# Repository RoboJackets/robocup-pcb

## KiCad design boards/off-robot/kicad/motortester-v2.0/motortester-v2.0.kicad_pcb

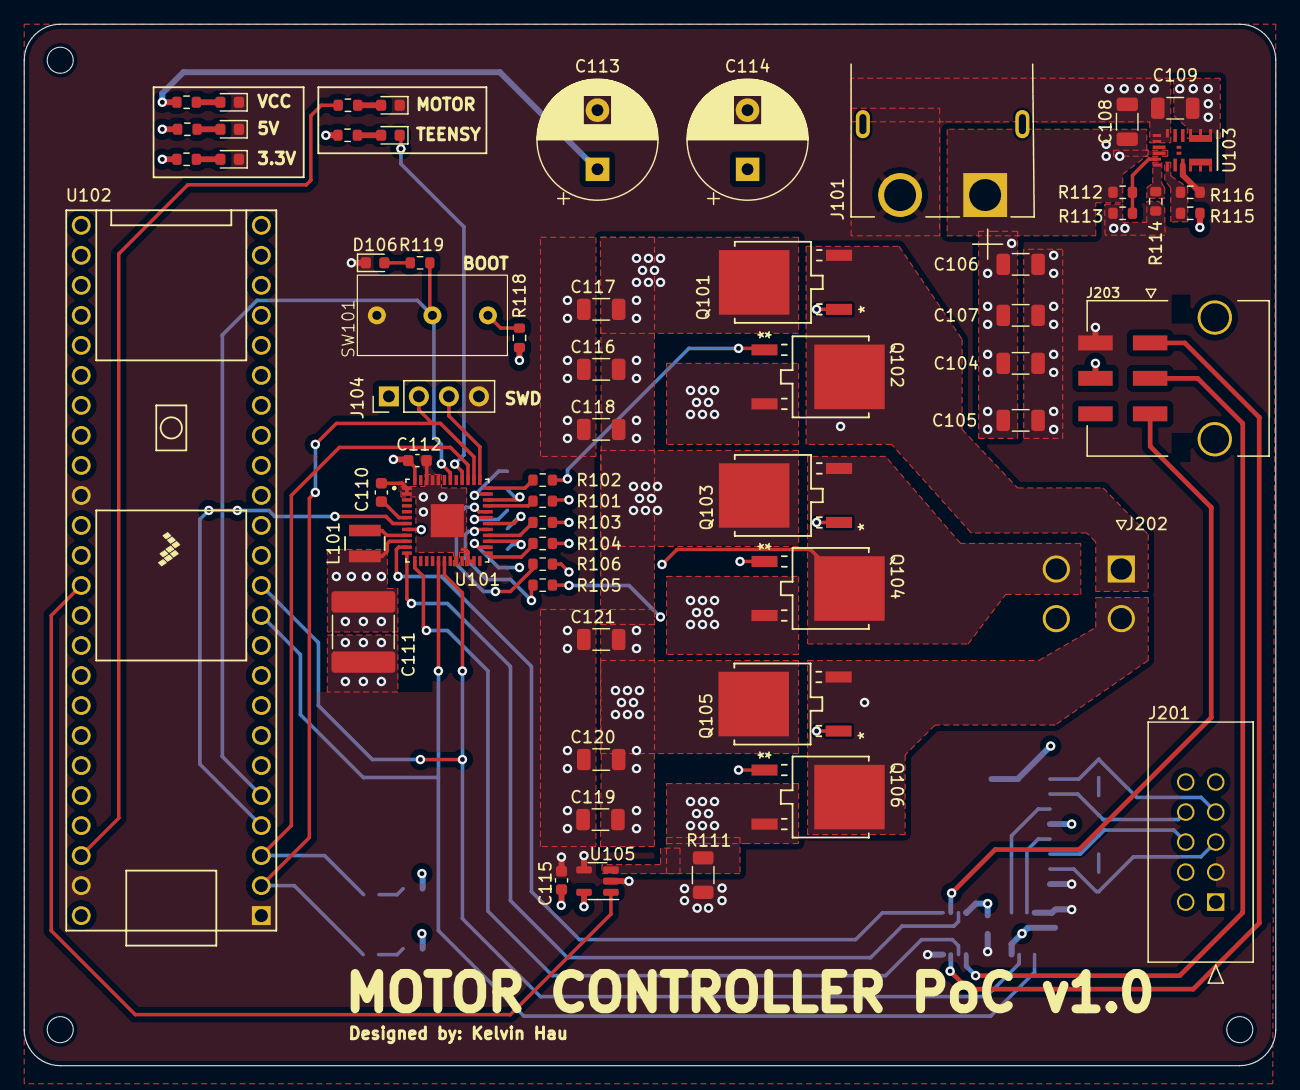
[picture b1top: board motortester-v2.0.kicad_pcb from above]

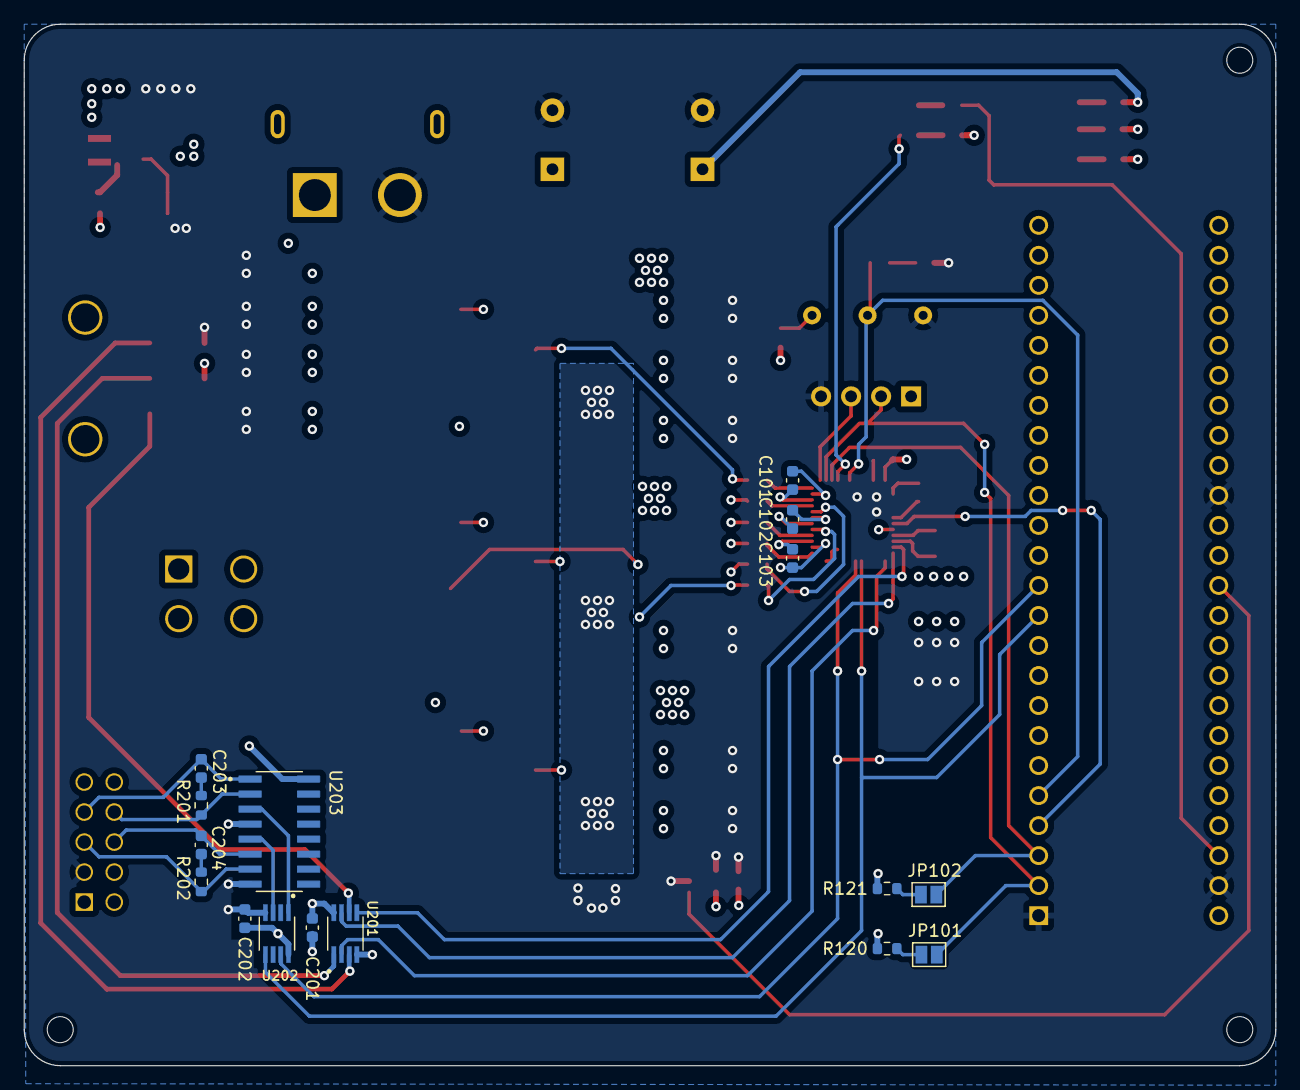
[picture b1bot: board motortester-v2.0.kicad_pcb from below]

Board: 4 copper layers, 105.9 x 88.1 mm, 79 parts (16 on the bottom side), 61 nets.

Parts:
C101, C102, C103, C112, C115, C201, C202: 100nF; C_0603_1608Metric
C104, C105, C106, C107, C108, C116, C117, C118, C119, C120, C121: 10uF; C_1206_3216Metric
C109: 22uF; C_1206_3216Metric
C110: 1uF; C_0603_1608Metric
C111: 47uF; C_2220_5750Metric
C113, C114: 220uF; CP_Radial_D10.0mm_P5.00mm
C203, C204: 0.1nF; C_0603_1608Metric
D101, D102, D103, D104, D105, D106: GREEN; D_0603_1608Metric
H201, H202, H203: MountingHole; MountingHole_2.2mm_M2
J101: XT60PW-M; AMASS_XT60PW-M
J104: SWD; PinHeader_1x04_P2.54mm_Vertical
J201: 702461004; CON_702461004_MOL
J202: 1x4_Molex_Connector; MOLEX_353180420
J203: 430450607; MOLEX_430450607
JP101, JP102: SolderJumper_2_Open; SolderJumper-2_P1.3mm_Open_Pad1.0x1.5mm
L101: 22uH; SRN3015
Q101, Q102, Q103, Q104, Q105, Q106: STD140N6F7; DPAKTO-252_A2_STM
R101, R102, R103, R104, R105, R106, R201, R202: 62; R_0603_1608Metric
R107, R109, R110, R117, R119: 1k; R_0603_1608Metric
R108: 4.7k; R_0603_1608Metric
R111: 2m; R_1206_3216Metric
R112: 270k; R_0603_1608Metric
R113, R120, R121: 100k; R_0603_1608Metric
R114: 63.4k; R_0603_1608Metric
R115: 160k; R_0603_1608Metric
R116: 30.1k; R_0603_1608Metric
R118: 10k; R_0603_1608Metric
SW101: SW_SPDT; Slide_Switch_SPDT
U101: STSPIN32F0A; IC_STSPIN32F0A
U102: Teensy4.1; Teensy41
U103: MPM3620GQV-P
U105: INA180A3; SOT-23-5
U201, U202: SN74LVC3G17DCTR; SOP65P400X130-8N
U203: MC3486DR; SOIC127P600X175-16N

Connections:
+3.3V: C111.1, C112.2, C115.1, C201.1, C202.1, J104.1, L101.1, R109.2, R110.2, R118.1, R120.2, R121.2, U101.10 (VDDA), U101.48 (VDD), U105.5 (V+), U201.8 (VCC), U202.8 (VCC)
+5V: C109.1, J201.2, J203.5, R115.2, R117.2, U102.48 (VIN), U103.7 (OUT), U103.8 (OUT), U103.9 (OUT), U203.4 (1,2EN), U203.16 (VCC)
BOOT_0: R119.2, SW101.2 (B), U101.42 (BOOT0), U102.5 (3_LRCLK2)
ENCA: U101.17 (PA6), U102.11 (9_OUT1C), U202.5 (2Y)
ENCA_N: J201.5, R202.1, U203.7 (2B)
ENCA_O: U202.3 (2A), U203.5 (2Y)
ENCA_P: C204.1, J201.6, U203.6 (2A)
ENCB: U101.18 (PA7), U102.12 (10_CS_MQSR), U202.7 (1Y)
ENCB_N: C203.2, J201.7, U203.1 (1B)
ENCB_O: U202.1 (1A), U203.3 (1Y)
ENCB_P: J201.8, R201.2, U203.2 (1A)
GND: C104.2, C105.2, C106.2, C107.2, C108.2, C109.2, C110.2, C111.2, C112.1, C113.2, C114.2, C115.2, C116.2, C117.2, C118.2, C119.2, C120.2, C121.2, C201.2, C202.2, D101.1 (K), D102.1 (K), D103.1 (K), D105.1 (K), D106.1 (K), J101.2 (-), J104.4, J201.3, J203.4, R111.2, R113.1, R114.1, R116.1, SW101.3 (C), U101.1 (OP2P), U101.2 (OP2N), U101.20 (TESTMODE), U101.22 (OP1N), U101.23 (OP1P), U101.44 (GND), U101.45 (OP3P), U101.46 (OP3N), U101.49 (EPAD), U102.1 (GND), U102.34 (GND), U102.47 (GND), U103.3 (AGND), U103.12 (PGND), U103.13 (PGND), U103.14 (PGND), U105.2 (GND), U105.4 (-), U201.4 (GND), U202.4 (GND), U203.8 (GND)
H1: U101.11 (PA0), U201.5 (2Y)
H1_M: J203.1, U201.3 (2A)
H2: U101.12 (PA1), U201.7 (1Y)
H2_M: J203.2, U201.1 (1A)
H3: U101.13 (PA2), U201.2 (3Y)
H3_M: J203.3, U201.6 (3A)
HSU: R101.1, U101.33 (HSU)
HSV: R105.1, U101.29 (HSV)
HSW: R104.1, U101.25 (HSW)
ISENSE: U102.37 (15_A1_RX3_SPDIF_IN), U105.1
LSU: R102.1, U101.36 (LSU)
LSV: R106.1, U101.32 (LSV)
LSW: R103.1, U101.28 (LSW)
MOTOR_LED: D104.1 (K), U101.40 (PB6)
NRST: U101.7 (NRST), U102.4 (2_OUT2)
unnamed: C203.1, R201.1
unnamed: C204.2, R202.2
unnamed: D101.2 (A), R107.1
unnamed: D102.2 (A), R108.1
unnamed: D103.2 (A), R109.1
unnamed: D104.2 (A), R110.1
unnamed: D105.2 (A), R117.1
unnamed: D106.2 (A), R119.1
unnamed: JP101.2 (B), R120.1
unnamed: JP102.2 (B), R121.1
unnamed: Q101.1 (G), R101.2
unnamed: Q102.1 (G), R102.2
unnamed: Q102.3 (S), Q104.3 (S), Q106.3 (S), R111.1, U105.3 (+)
unnamed: Q103.1 (G), R103.2
unnamed: Q104.1 (G), R104.2
unnamed: Q105.1 (G), R105.2
unnamed: Q106.1 (G), R106.2
unnamed: R107.2, U102.46 (3V3)
unnamed: R118.2, SW101.1 (A)
unnamed: L101.2, U101.9 (SW)
unnamed: C101.1, U101.35 (VBOOTU)
unnamed: C102.1, U101.31 (VBOOTV)
unnamed: C103.1, U101.27 (VBOOTW)
unnamed: C110.1, U101.6 (VREG12)
unnamed: R114.2, U103.18 (AAM)
unnamed: R112.1, R113.2, U103.17 (EN)
unnamed: R115.1, R116.2, U103.1 (FB)
PHASE_U: C101.2, J202.1, Q101.3 (S), Q102.2 (D), U101.34 (OUTU)
PHASE_V: C102.2, J202.2, Q105.3 (S), Q106.2 (D), U101.30 (OUTV)
PHASE_W: C103.2, J202.3, Q103.3 (S), Q104.2 (D), U101.26 (OUTW)
SWD_CLK: J104.2, JP101.1 (A), U101.38 (PA14_SWD_CLK), U102.2 (0_RX1_CRX2_CS1)
SWD_IO: J104.3, U101.37 (PA13_SWD_IO)
USART1_RX: JP102.1 (A), U101.39 (PA15), U102.3 (1_TX1_CTX2_MISO1)
VCC: C104.1, C105.1, C106.1, C107.1, C108.1, C113.1, C114.1, C116.1, C117.1, C118.1, C119.1, C120.1, C121.1, J101.1 (+), Q101.2 (D), Q103.2 (D), Q105.2 (D), R108.2, R112.2, U101.8 (VM), U103.16 (IN)

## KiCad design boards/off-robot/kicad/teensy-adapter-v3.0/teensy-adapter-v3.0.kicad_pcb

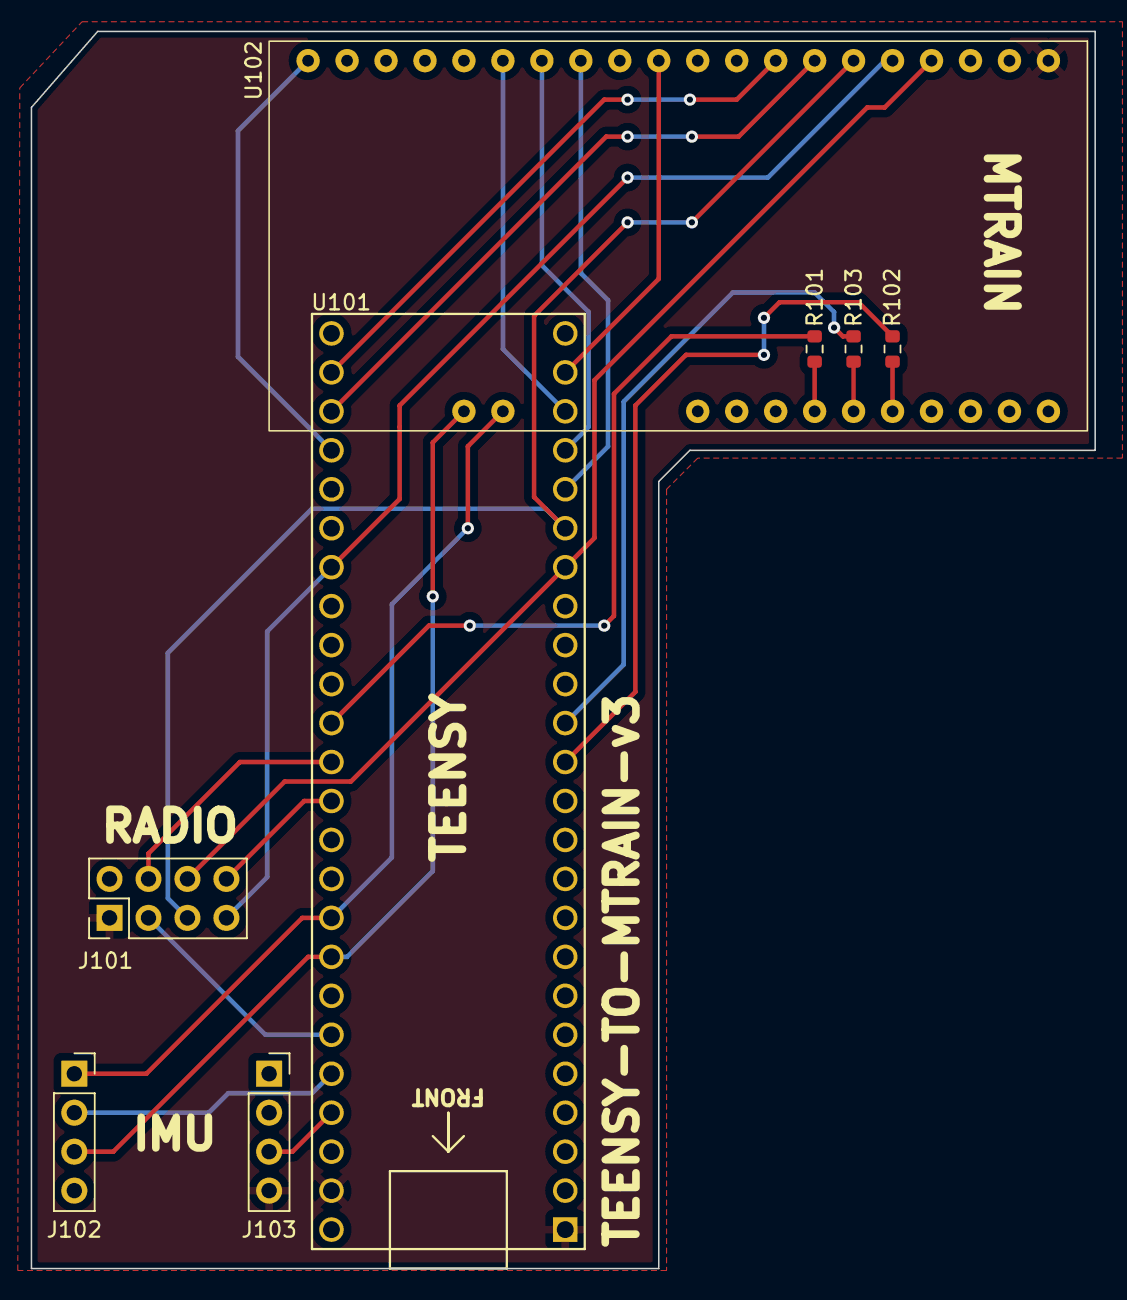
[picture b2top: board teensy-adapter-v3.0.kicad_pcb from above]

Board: 4 copper layers, 69.3 x 80.6 mm, 8 parts (0 on the bottom side), 27 nets.

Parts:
J101: Conn_02x04_Odd_Even; PinHeader_2x04_P2.54mm_Vertical
J102: IMU_Left; PinSocket_1x04_P2.54mm_Vertical
J103: IMU_Right; PinSocket_1x04_P2.54mm_Vertical
R101, R102, R103: 0; R_0603_1608Metric
U101: Teensy4.1; Teensy41
U102: mTrain

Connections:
+3V3: J101.2, J102.4, J103.1, U101.46 (3V3), U102.40 (VDD)
+5V: U101.48 (VIN), U102.2 (VIN)
ADDR_IMU: J102.2, U101.44 (22_A8_CTX1)
CE_RADIO: J101.3, U101.43 (21_A7_RX5_BCLK1)
CS_DOT: U101.23 (31_CTX3), U102.11
CS_FPGA: U101.12 (10_CS_MQSR), U102.31
CS_KICK: U101.26 (34_RX8), U102.8
CS_RADIO: J101.4, U101.36 (14_A0_TX3_SPDIF_OUT)
FPGA_DONE: U101.22 (30_CRX3), U102.15
FPGA_INIT: U101.21 (29_TX7), U102.14
FPGA_MISO: R103.1, U102.35
FPGA_MOSI: R102.1, U102.36
FPGA_PROG: U101.20 (28_RX7), U102.13
FPGA_SCK: R101.2, U102.34
GND: J101.1, J103.4, U101.1 (GND), U101.47 (GND), U102.1 (GND)
INT_IMU: J103.3, U101.45 (23_A9_CRX1_MCLK1)
INT_IO: U101.28 (36_CS), U102.20
INT_RADIO: J101.8, U101.37 (15_A1_RX3_SPDIF_IN)
MISO: J101.7, U101.31 (39_MISO1_OUT1A), U102.5
MOSI: J101.6, U101.18 (26_A12_MOSI1), U102.4
unnamed: R102.2, U101.13 (11_MOSI_CTX1)
unnamed: R103.2, U101.14 (12_MISO_MQSL)
unnamed: R101.1, U101.35 (13_SCK_LED)
RST_KICK: U101.27 (35_TX8), U102.7
SCK: J101.5, U101.19 (27_A13_SCK1), U102.6
SCL: J102.3, U101.41 (19_A5_SCL), U102.25
SDA: J102.1, U101.40 (18_A4_SDA), U102.26

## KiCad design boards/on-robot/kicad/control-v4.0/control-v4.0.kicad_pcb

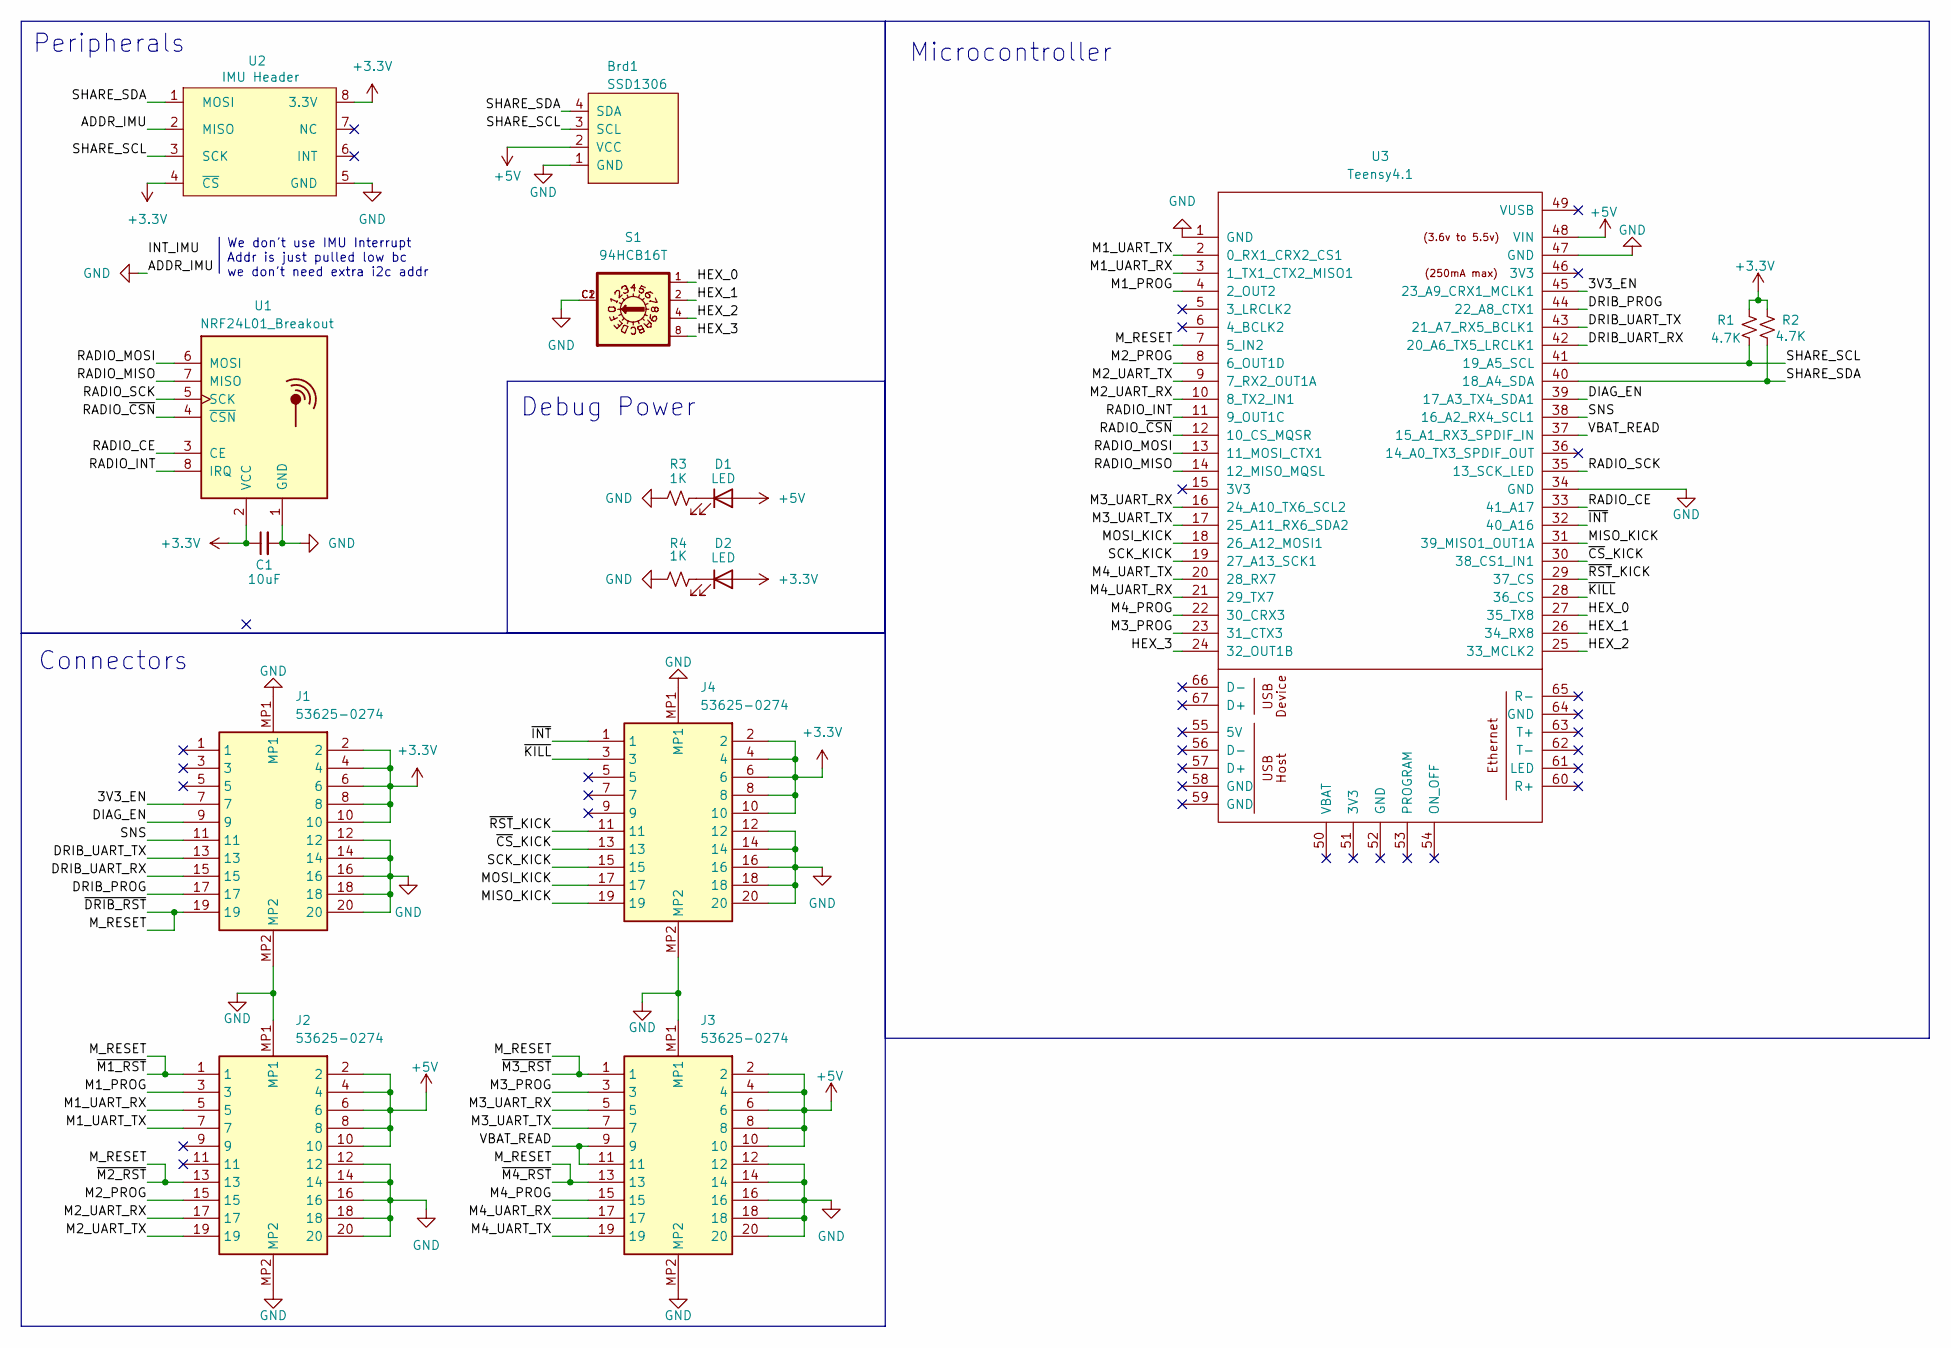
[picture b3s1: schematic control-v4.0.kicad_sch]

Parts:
Brd1: SSD1306; Adafruit_SSD1306_No_Mounting_Holes
C1: 10uF; C_0603_1608Metric
D1, D2: LED; D_0603_1608Metric
J1, J2, J3, J4: 53625-0274; 536250274; Manufacturer P/N 0536250274
R1, R2: 4.7K; R_0603_1608Metric
R3, R4: 1K; R_0603_1608Metric
S1: 94HCB16T; HEX
U1: NRF24L01_Breakout; nRF24L01_Breakout
U2: IMU Header; HeaderIMUFooter
U3: Teensy4.1; Teensy41

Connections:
+3.3V: C1.1, D2.2 (A), J1.2, J1.4, J1.6, J1.8, J1.10, J4.2, J4.4, J4.6, J4.8, J4.10, R1.2, R2.2, U1.2 (VCC), U2.4 (~CS), U2.8 (3.3V)
+5V: Brd1.2 (VCC), D1.2 (A), J2.2, J2.4, J2.6, J2.8, J2.10, J3.2, J3.4, J3.6, J3.8, J3.10, U3.48 (VIN)
/3V3_EN: J1.7, U3.45 (23_A9_CRX1_MCLK1)
/DIAG_EN: J1.9, U3.39 (17_A3_TX4_SDA1)
/DRIB_PROG: J1.17, U3.44 (22_A8_CTX1)
/DRIB_UART_RX: J1.15, U3.42 (20_A6_TX5_LRCLK1)
/DRIB_UART_TX: J1.13, U3.43 (21_A7_RX5_BCLK1)
/HEX_0: S1.1, U3.27 (35_TX8)
/HEX_1: S1.2, U3.26 (34_RX8)
/HEX_2: S1.4, U3.25 (33_MCLK2)
/HEX_3: S1.8, U3.24 (32_OUT1B)
/M1_PROG: J2.3, U3.4 (2_OUT2)
/M1_UART_RX: J2.5, U3.3 (1_TX1_CTX2_MISO1)
/M1_UART_TX: J2.7, U3.2 (0_RX1_CRX2_CS1)
/M2_PROG: J2.15, U3.8 (6_OUT1D)
/M2_UART_RX: J2.17, U3.10 (8_TX2_IN1)
/M2_UART_TX: J2.19, U3.9 (7_RX2_OUT1A)
/M3_PROG: J3.3, U3.23 (31_CTX3)
/M3_UART_RX: J3.5, U3.16 (24_A10_TX6_SCL2)
/M3_UART_TX: J3.7, U3.17 (25_A11_RX6_SDA2)
/M4_PROG: J3.15, U3.22 (30_CRX3)
/M4_UART_RX: J3.17, U3.21 (29_TX7)
/M4_UART_TX: J3.19, U3.20 (28_RX7)
/MISO_KICK: J4.19, U3.31 (39_MISO1_OUT1A)
/MOSI_KICK: J4.17, U3.18 (26_A12_MOSI1)
/M_RESET: J1.19, J2.1, J2.13, J3.1, J3.13, U3.7 (5_IN2)
/RADIO_CE: U1.3 (CE), U3.33 (41_A17)
/RADIO_INT: U1.8 (IRQ), U3.11 (9_OUT1C)
/RADIO_MISO: U1.7 (MISO), U3.14 (12_MISO_MQSL)
/RADIO_MOSI: U1.6 (MOSI), U3.13 (11_MOSI_CTX1)
/RADIO_SCK: U1.5 (SCK), U3.35 (13_SCK_LED)
/RADIO_~CSN: U1.4 (~CSN), U3.12 (10_CS_MQSR)
/SCK_KICK: J4.15, U3.19 (27_A13_SCK1)
/SHARE_SCL: Brd1.3 (SCL), R1.1, U2.3 (SCK), U3.41 (19_A5_SCL)
/SHARE_SDA: Brd1.4 (SDA), R2.1, U2.1 (MOSI), U3.40 (18_A4_SDA)
/SNS: J1.11, U3.38 (16_A2_RX4_SCL1)
/VBAT_READ: J3.9, J3.11, U3.37 (15_A1_RX3_SPDIF_IN)
/~CS_KICK: J4.13, U3.30 (38_CS1_IN1)
/~INT: J4.1, U3.32 (40_A16)
/~KILL: J4.3, U3.28 (36_CS)
/~RST_KICK: J4.11, U3.29 (37_CS)
GND: Brd1.1 (GND), C1.2, J1.12, J1.14, J1.16, J1.18, J1.20, J1.MP1, J1.MP2, J2.12, J2.14, J2.16, J2.18, J2.20, J2.MP1, J2.MP2, J3.12, J3.14, J3.16, J3.18, J3.20, J3.MP1, J3.MP2, J4.12, J4.14, J4.16, J4.18, J4.20, J4.MP1, J4.MP2, R3.1, R4.1, S1.C1, S1.C2, U1.1 (GND), U2.2 (MISO), U2.5 (GND), U3.1 (GND), U3.34 (GND), U3.47 (GND)
unnamed: D1.1 (K), R3.2
unnamed: D2.1 (K), R4.2

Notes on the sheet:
Debug Power
We don't use IMU Interrupt Addr is just pulled low bc we don't need extra i2c addr
Peripherals
Microcontroller
Connectors

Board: 2 copper layers, 16 parts (9 on the bottom side), 44 nets, no tracks yet.

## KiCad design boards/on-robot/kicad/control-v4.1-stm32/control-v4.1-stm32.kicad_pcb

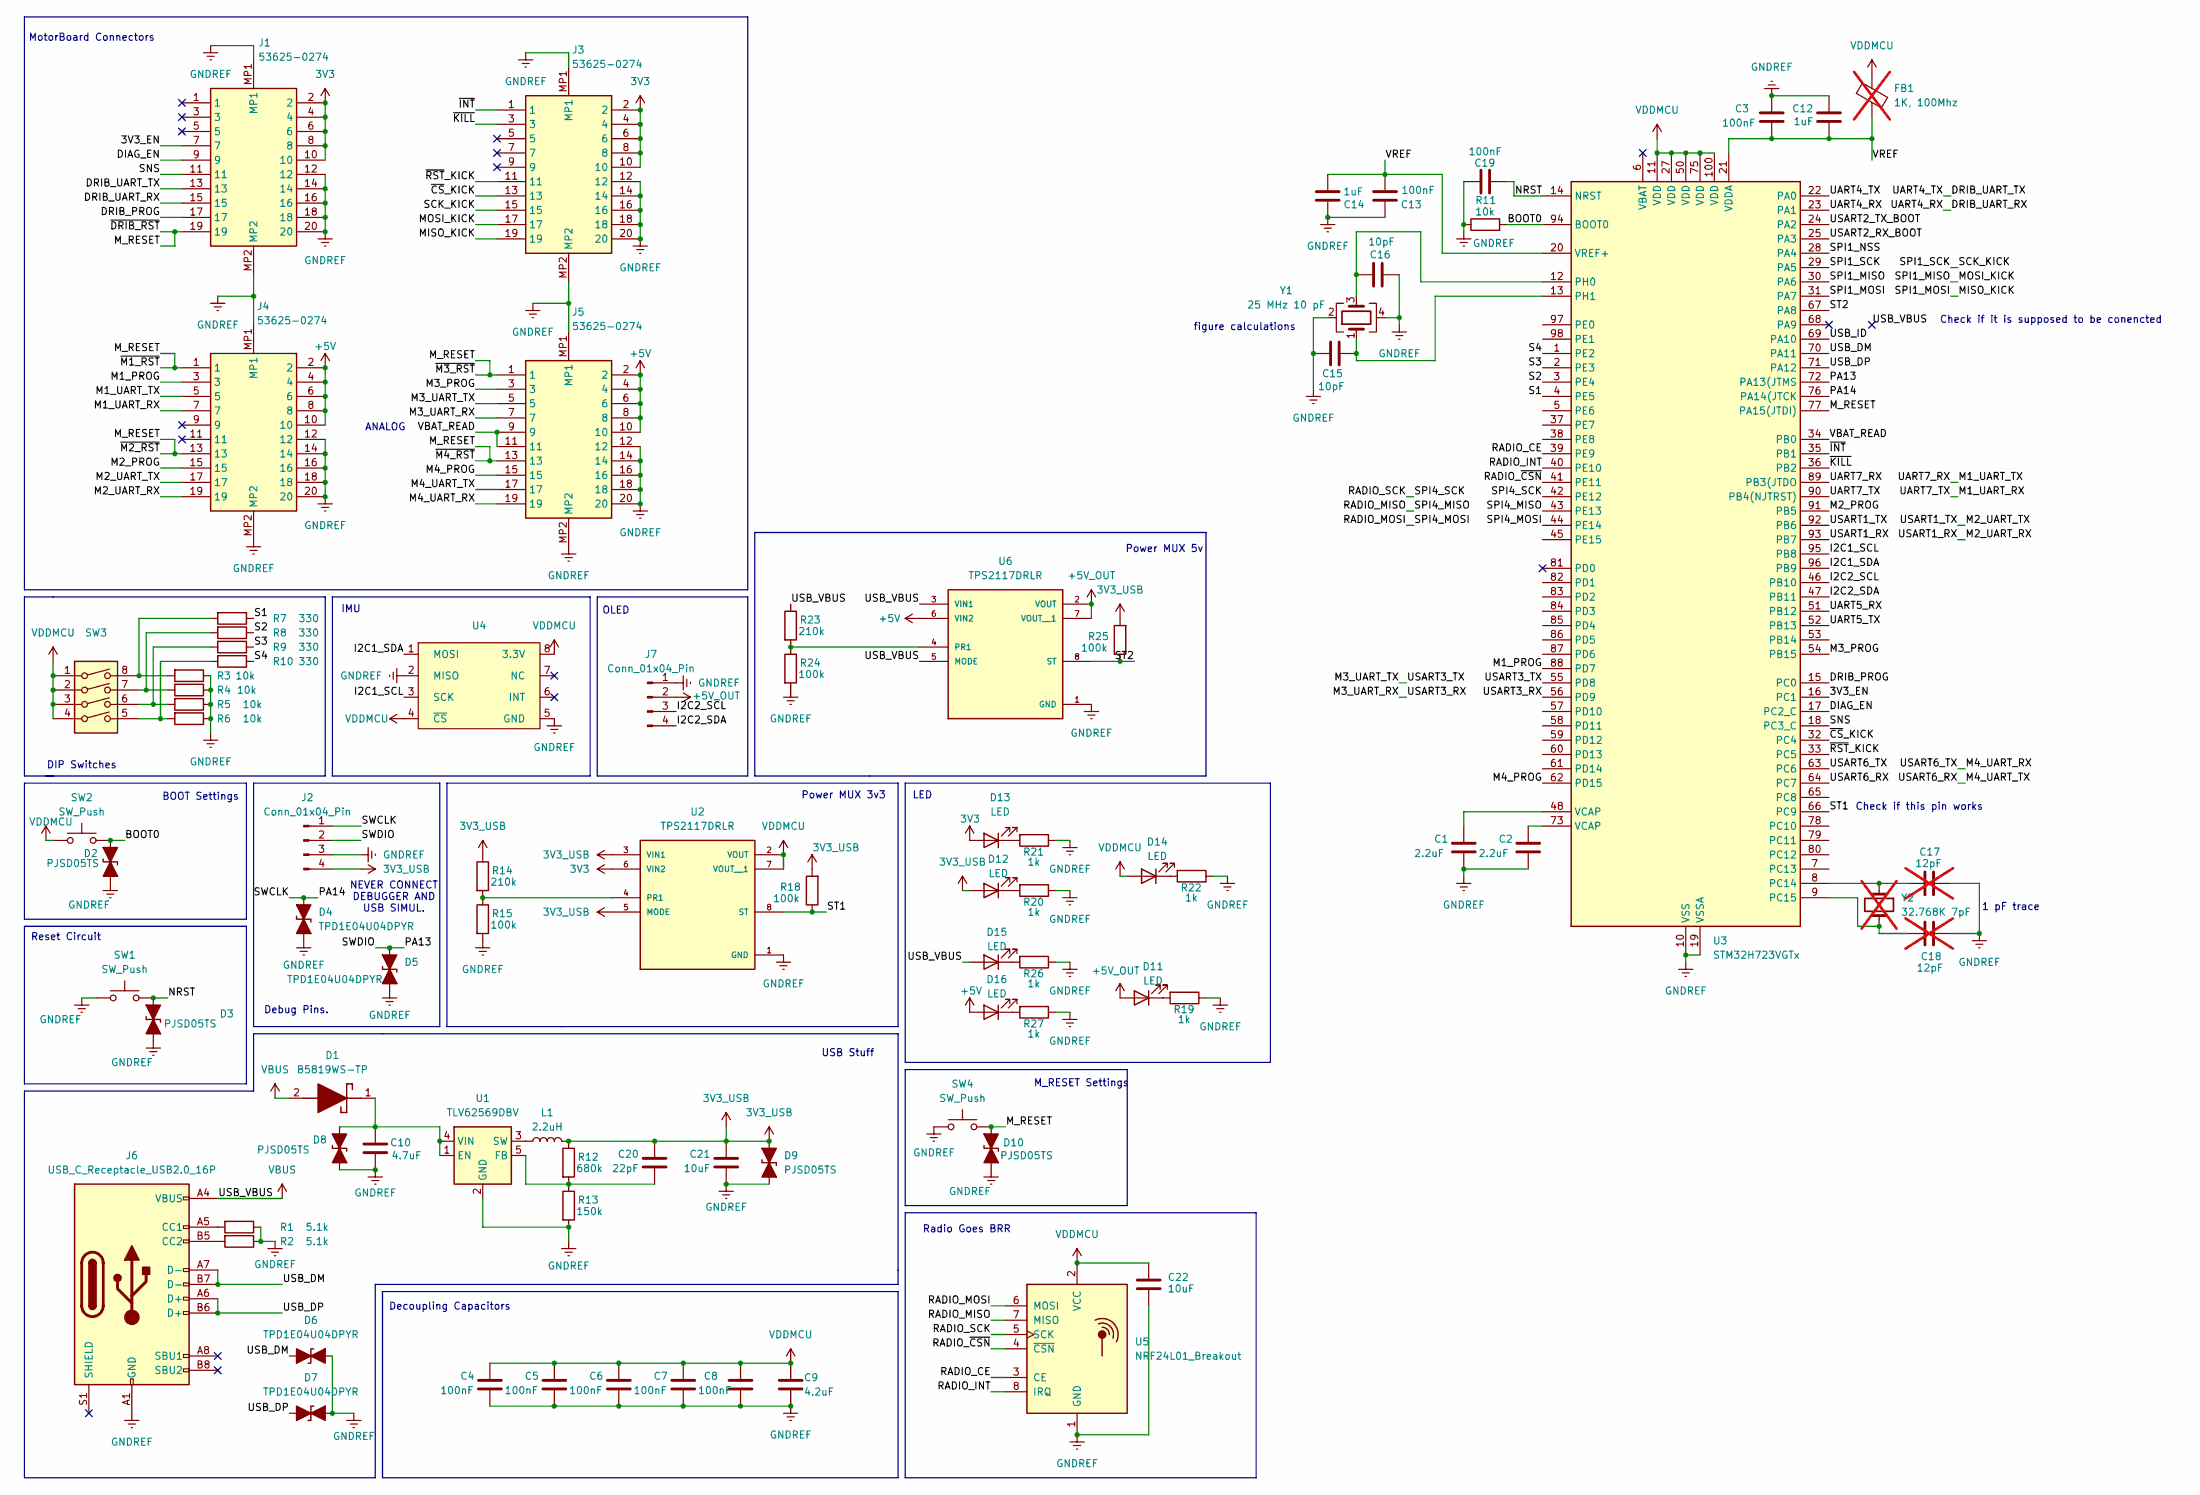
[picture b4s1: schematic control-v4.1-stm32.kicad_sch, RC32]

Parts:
C1, C2: 2.2uF; C_0603_1608Metric
C3, C4, C5, C6, C7, C8, C13, C19: 100nF; C_0603_1608Metric
C9: 4.2uF; C_0603_1608Metric
C10: 4.7uF; C_0603_1608Metric
C12, C14: 1uF; C_0603_1608Metric
C15, C16: 10pF; C_0603_1608Metric
C17, C18: 12pF; C_0603_1608Metric; not fitted
C20: 22pF; C_0603_1608Metric
C21, C22: 10uF; C_0603_1608Metric
D1: B5819WS-TP; SOD2512X115N; Mouser Part Number 833-B5819WS-TP
D2, D3, D8, D9, D10: PJSD05TS; SOD-523_0P9X1P3_ONS
D4, D5, D6, D7: TPD1E04U04DPYR; DPY2_TEX
D11, D12, D13, D14, D15, D16: LED; D_0603_1608Metric
FB1: 1K, 100Mhz; BEADC1608X95N; not fitted
J1, J3, J4, J5: 53625-0274; 536250274; Manufacturer P/N 0536250274
J2: Conn_01x04_Pin; PinHeader_1x04_P2.54mm_Vertical
J6: USB_C_Receptacle_USB2.0_16P; USB_C_Receptacle_GCT_USB4110
J7: Conn_01x04_Pin; Adafruit_SSD1306_No_Mounting_Holes
L1: 2.2uH; L_0603_1608Metric
R1, R2: 5.1k; R_0603_1608Metric
R3, R4, R5, R6, R11: 10k; R_0603_1608Metric
R7, R8, R9, R10: 330; R_0603_1608Metric
R12: 680k; R_0603_1608Metric
R13: 150k; R_0603_1608Metric
R14, R23: 210k; R_0603_1608Metric
R15, R18, R24, R25: 100k; R_0603_1608Metric
R19, R20, R21, R22, R26, R27: 1k; R_0603_1608Metric
SW1, SW2, SW4: SW_Push; SW_PUSH_6mm
SW3: SW_DIP_SPSTx04_Slide_9.78x12.34mm_W7.62mm_P2.54mm
U1: TLV62569DBV; SOT-23-5
U2, U6: TPS2117DRLR; SOTFL50P160X60-8N; PARTREV A
U3: STM32H723VGTx; LQFP-100_14x14mm_P0.5mm
U4: HeaderIMUFooter
U5: NRF24L01_Breakout; nRF24L01_Breakout
Y1: 25 MHz 10 pF; XTAL_ABM8-25.000MHz-10-B1U-T
Y2: 32.768K 7pF; XTAL_ABS07-32.768KHZ-T; not fitted

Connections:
3V3: D13.2 (A), J1.2, J1.4, J1.6, J1.8, J1.10, J3.2, J3.4, J3.6, J3.8, J3.10, U2.6 (VIN2)
3V3_USB: C20.1, C21.1, D9.1 (A1), D12.2 (A), J2.4, L1.2, R12.1, R14.1, R18.2, R25.2, U2.3 (VIN1), U2.5 (MODE)
+5V: D16.2 (A), J4.2, J4.4, J4.6, J4.8, J4.10, J5.2, J5.4, J5.6, J5.8, J5.10, U6.6 (VIN2)
+5V_OUT: D11.2 (A), J7.2, U6.2 (VOUT), U6.7 (VOUT__1)
/3V3_EN: J1.7, U3.16 (PC1)
/BOOT0: D2.2 (A2), R11.2, SW2.2, U3.94 (BOOT0)
/DIAG_EN: J1.9, U3.17 (PC2_C)
/DRIB_PROG: J1.17, U3.15 (PC0)
/DRIB_UART_RX: J1.15, U3.23 (PA1)
/DRIB_UART_TX: J1.13, U3.22 (PA0)
/I2C1_SCL: U3.95 (PB8), U4.3 (SCK)
/I2C1_SDA: U3.96 (PB9), U4.1 (MOSI)
/I2C2_SCL: J7.3, U3.46 (PB10)
/I2C2_SDA: J7.4, U3.47 (PB11)
/M1_PROG: J4.3, U3.88 (PD7)
/M1_UART_RX: J4.7, U3.90 (PB4(NJTRST))
/M1_UART_TX: J4.5, U3.89 (PB3(JTDO)
/M2_PROG: J4.15, U3.91 (PB5)
/M2_UART_RX: J4.19, U3.93 (PB7)
/M2_UART_TX: J4.17, U3.92 (PB6)
/M3_PROG: J5.3, U3.54 (PB15)
/M3_UART_RX: J5.7, U3.56 (PD9)
/M3_UART_TX: J5.5, U3.55 (PD8)
/M4_PROG: J5.15, U3.62 (PD15)
/M4_UART_RX: J5.19, U3.63 (PC6)
/M4_UART_TX: J5.17, U3.64 (PC7)
/MISO_KICK: J3.19, U3.31 (PA7)
/MOSI_KICK: J3.17, U3.30 (PA6)
/M_RESET: D10.2 (A2), J1.19, J4.1, J4.13, J5.1, J5.13, SW4.2, U3.77 (PA15(JTDI))
/NRST: C19.1, D3.2 (A2), SW1.2, U3.14 (NRST)
/PA13: D5.2 (A2), J2.2, U3.72 (PA13(JTMS)
/PA14: D4.2 (A2), J2.1, U3.76 (PA14(JTCK)
/RADIO_CE: U3.39 (PE9), U5.3 (CE)
/RADIO_INT: U3.40 (PE10), U5.8 (IRQ)
/RADIO_MISO: U3.43 (PE13), U5.7 (MISO)
/RADIO_MOSI: U3.44 (PE14), U5.6 (MOSI)
/RADIO_SCK: U3.42 (PE12), U5.5 (SCK)
/RADIO_~CSN: U3.41 (PE11), U5.4 (~CSN)
/S1: R7.1, U3.4 (PE5)
/S2: R8.1, U3.3 (PE4)
/S3: R9.1, U3.2 (PE3)
/S4: R10.1, U3.1 (PE2)
/SCK_KICK: J3.15, U3.29 (PA5)
/SNS: J1.11, U3.18 (PC3_C)
/SPI1_NSS: U3.28 (PA4)
/ST1: R18.1, U2.8 (ST), U3.66 (PC9)
/ST2: R25.1, U3.67 (PA8), U6.8 (ST)
/UART5_RX: U3.51 (PB12)
/UART5_TX: U3.52 (PB13)
/USART2_RX_BOOT: U3.25 (PA3)
/USART2_TX_BOOT: U3.24 (PA2)
/USB_DM: D6.1 (A1), J6.A7 (D-), J6.B7 (D-), U3.70 (PA11)
/USB_DP: D7.1 (A1), J6.A6 (D+), J6.B6 (D+), U3.71 (PA12)
/USB_ID: U3.69 (PA10)
/VBAT_READ: J5.9, J5.11, U3.34 (PB0)
/VREF: C3.2, C12.2, C13.2, C14.2, FB1.2, U3.20 (VREF+), U3.21 (VDDA)
/~CS_KICK: J3.13, U3.32 (PC4)
/~INT: J3.1, U3.35 (PB1)
/~KILL: J3.3, U3.36 (PB2)
/~RST_KICK: J3.11, U3.33 (PC5)
unnamed: C1.1, U3.48 (VCAP)
unnamed: C2.1, U3.73 (VCAP)
unnamed: D11.1 (K), R19.2
unnamed: D12.1 (K), R20.2
unnamed: D13.1 (K), R21.2
unnamed: D14.1 (K), R22.2
unnamed: D15.1 (K), R26.2
unnamed: D16.1 (K), R27.2
unnamed: J6.A5 (CC1), R1.2
unnamed: J6.B5 (CC2), R2.2
unnamed: R3.2, R7.2, SW3.8
unnamed: R4.2, R8.2, SW3.7
unnamed: R5.2, R9.2, SW3.6
unnamed: R6.2, R10.2, SW3.5
unnamed: C20.2, R12.2, R13.1, U1.5 (FB)
unnamed: L1.1, U1.3 (SW)
unnamed: R14.2, R15.1, U2.4 (PR1)
unnamed: C17.1, U3.8 (PC14), Y2.1
unnamed: C18.1, U3.9 (PC15), Y2.2
unnamed: C16.2, U3.12 (PH0), Y1.3
unnamed: C15.2, U3.13 (PH1), Y1.1
unnamed: R23.2, R24.1, U6.4 (PR1)
VDDMCU: C4.1, C5.1, C6.1, C7.1, C8.1, C9.1, C22.1, D14.2 (A), FB1.1, SW2.1, SW3.1, SW3.2, SW3.3, SW3.4, U2.2 (VOUT), U2.7 (VOUT__1), U3.11 (VDD), U3.27 (VDD), U3.50 (VDD), U3.75 (VDD), U3.100 (VDD), U4.4 (~CS), U4.8 (3.3V), U5.2 (VCC)

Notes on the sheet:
Power MUX 3v3
Check if it is supposed to be conencted
NEVER CONNECT DEBUGGER AND USB SIMUL.
M_RESET Settings
ANALOG
Power MUX 5v
figure calculations
Radio Goes BRR
Debug Pins.
USB Stuff
Decoupling Capacitors
LED
DIP Switches
1 pF trace
BOOT Settings
IMU
MotorBoard Connectors
Check if this pin works
OLED
Reset Circuit

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
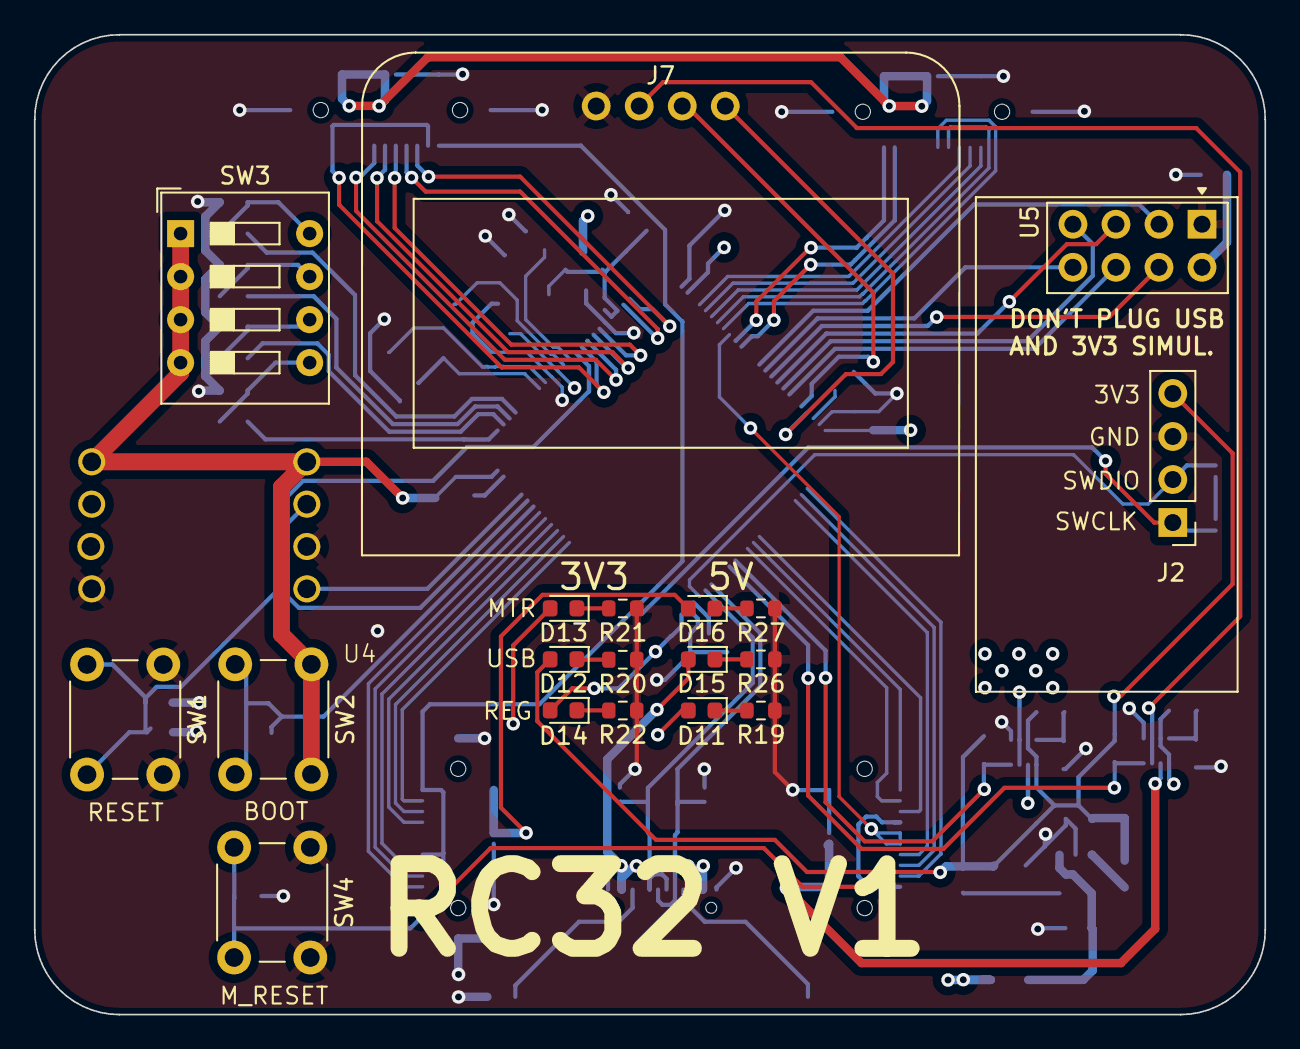
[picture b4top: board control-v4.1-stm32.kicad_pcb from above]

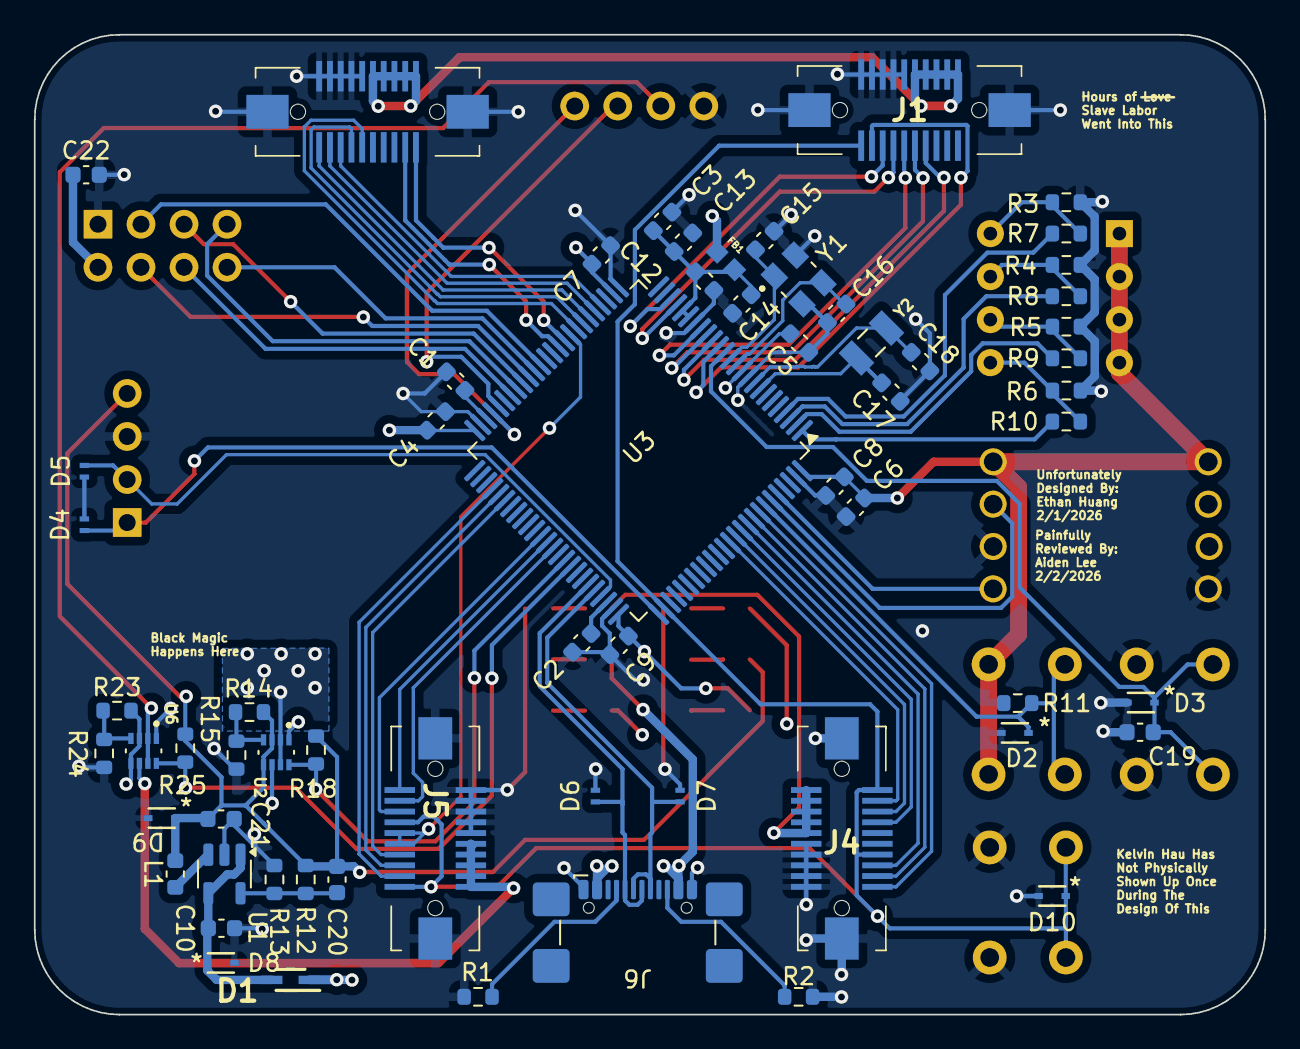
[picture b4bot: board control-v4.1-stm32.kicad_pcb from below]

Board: 4 copper layers, 72.7 x 57.8 mm, 83 parts (63 on the bottom side), 80 nets.
